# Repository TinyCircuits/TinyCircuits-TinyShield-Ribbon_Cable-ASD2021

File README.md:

# TinyCircuits TinyShield Ribbon Cable Board
# ASD2021 Rev1

The design files are located under design_files/ for the TinyCircuits ASD2021 Rev 1 PCB.  This is a TinyShield board that has a ribbon cable connector to allow connecting to another board using a ribbon cable.

Format is in Cadsoft Eagle format - Eagle version 6.2 was used for the original design.

For more infomation on this, check out the product page at TinyCircuits.com: https://tinycircuits.com/collections/proto-boards/products/tinyshield-ribbon-cable-extender

# License:

Design by TinyCircuits.
All design files are released under the Creative Commons Attribution Share-Alike 3.0 License, see the following link for details: http://creativecommons.org/licenses/by-sa/3.0

All text above must be included in any redistribution or derived design

This project uses designs and concepts developed as part of the Arduino project and the LilyPad project.  The TinyCircuits design files themselves (schematics, PCB and libraries) are not directly derived from these works' design files and have been created new, however the concepts and basic architecture behind the TinyDuino and TinyLily products are derived and we thank the hard work of the organizations below for their contributions to open-source hardware:
  
Original Arduino Uno Design by Team Arduino

LilyPad Arduino Design by Leah Buechley and Sparkfun Electronics

Please support the open-source hardware community

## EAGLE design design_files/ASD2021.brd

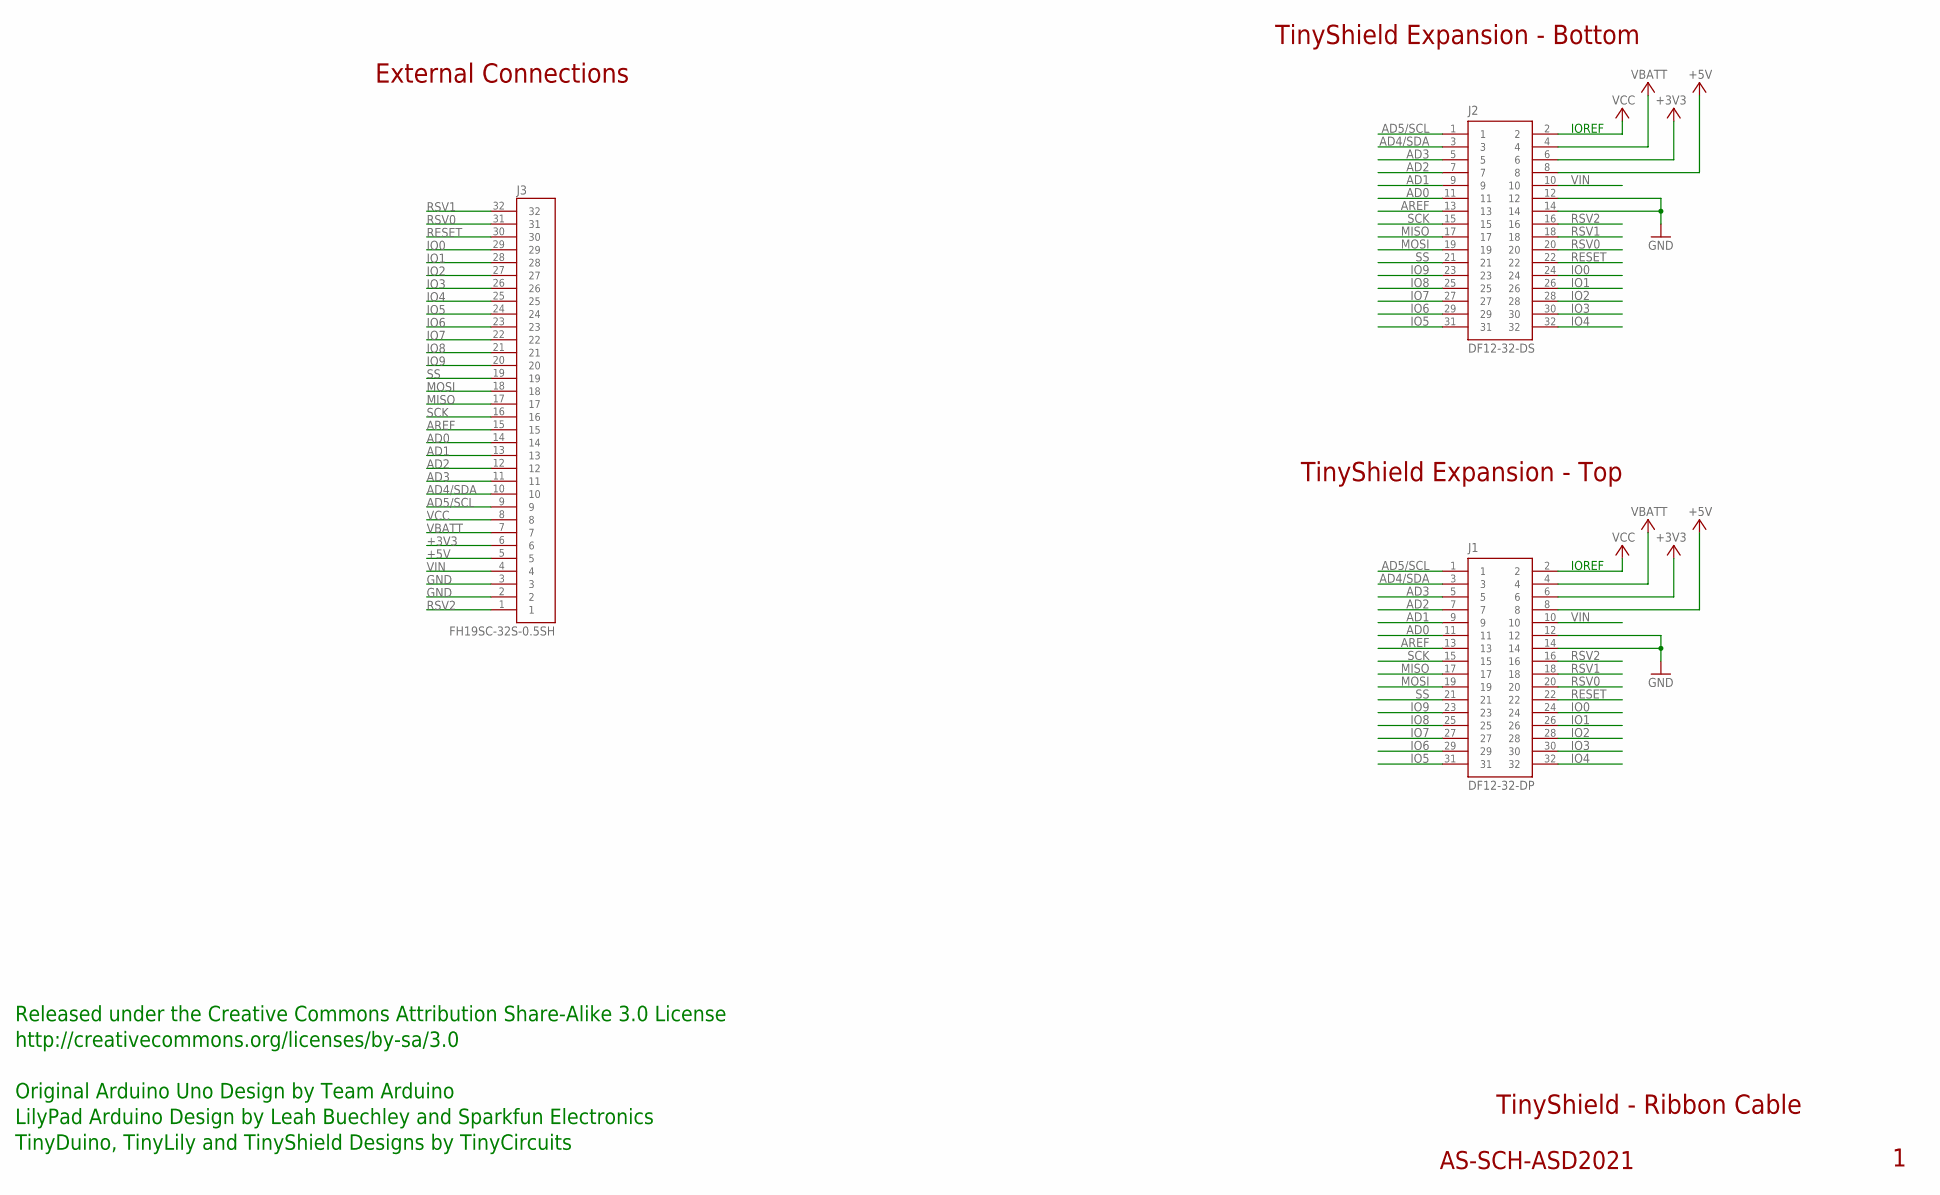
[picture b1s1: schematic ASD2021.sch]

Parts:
J1: DF12-32-DP; PARTNO AS-ITM-00015
J2: DF12-32-DS; PARTNO AS-ITM-00012
J3: FH19SC-32S-0.5SH

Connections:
+3V3: J1.6, J2.6, J3.6
+5V: J1.8, J2.8, J3.5
AD0: J1.11, J2.11, J3.14
AD1: J1.9, J2.9, J3.13
AD2: J1.7, J2.7, J3.12
AD3: J1.5, J2.5, J3.11
AD4/SDA: J1.3, J2.3, J3.10
AD5/SCL: J1.1, J2.1, J3.9
AREF: J1.13, J2.13, J3.15
GND: J1.12, J1.14, J2.12, J2.14, J3.2, J3.3
IO0: J1.24, J2.24, J3.29
IO1: J1.26, J2.26, J3.28
IO2: J1.28, J2.28, J3.27
IO3: J1.30, J2.30, J3.26
IO4: J1.32, J2.32, J3.25
IO5: J1.31, J2.31, J3.24
IO6: J1.29, J2.29, J3.23
IO7: J1.27, J2.27, J3.22
IO8: J1.25, J2.25, J3.21
IO9: J1.23, J2.23, J3.20
MISO: J1.17, J2.17, J3.17
MOSI: J1.19, J2.19, J3.18
RESET: J1.22, J2.22, J3.30
RSV0: J1.20, J2.20, J3.31
RSV1: J1.18, J2.18, J3.32
RSV2: J1.16, J2.16, J3.1
SCK: J1.15, J2.15, J3.16
SS: J1.21, J2.21, J3.19
VBATT: J1.4, J2.4, J3.7
VCC: J1.2, J2.2, J3.8
VIN: J1.10, J2.10, J3.4

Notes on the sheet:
TinyShield Expansion - Bottom
TinyShield - Ribbon Cable
AS-SCH-ASD2021
TinyShield Expansion - Top
IOREF
Released under the Creative Commons Attribution Share-Alike 3.0 License
http://creativecommons.org/licenses/by-sa/3.0
LilyPad Arduino Design by Leah Buechley and Sparkfun Electronics
TinyDuino, TinyLily and TinyShield Designs by TinyCircuits
Original Arduino Uno Design by Team Arduino
External Connections

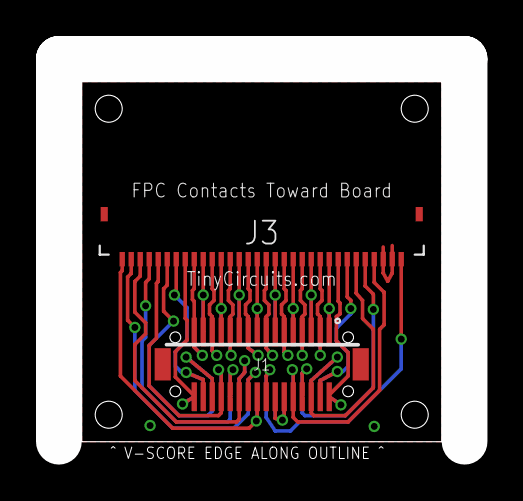
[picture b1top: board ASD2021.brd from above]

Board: 2 copper layers, 20.0 x 20.0 mm, 4 parts (1 on the bottom side), 31 nets.

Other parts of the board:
U$1: DOCFIELD-TINYCIRCUITS-PCB

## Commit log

2015-04-11 :tada: Added .gitattributes & .gitignore files
2019-01-04 update format
